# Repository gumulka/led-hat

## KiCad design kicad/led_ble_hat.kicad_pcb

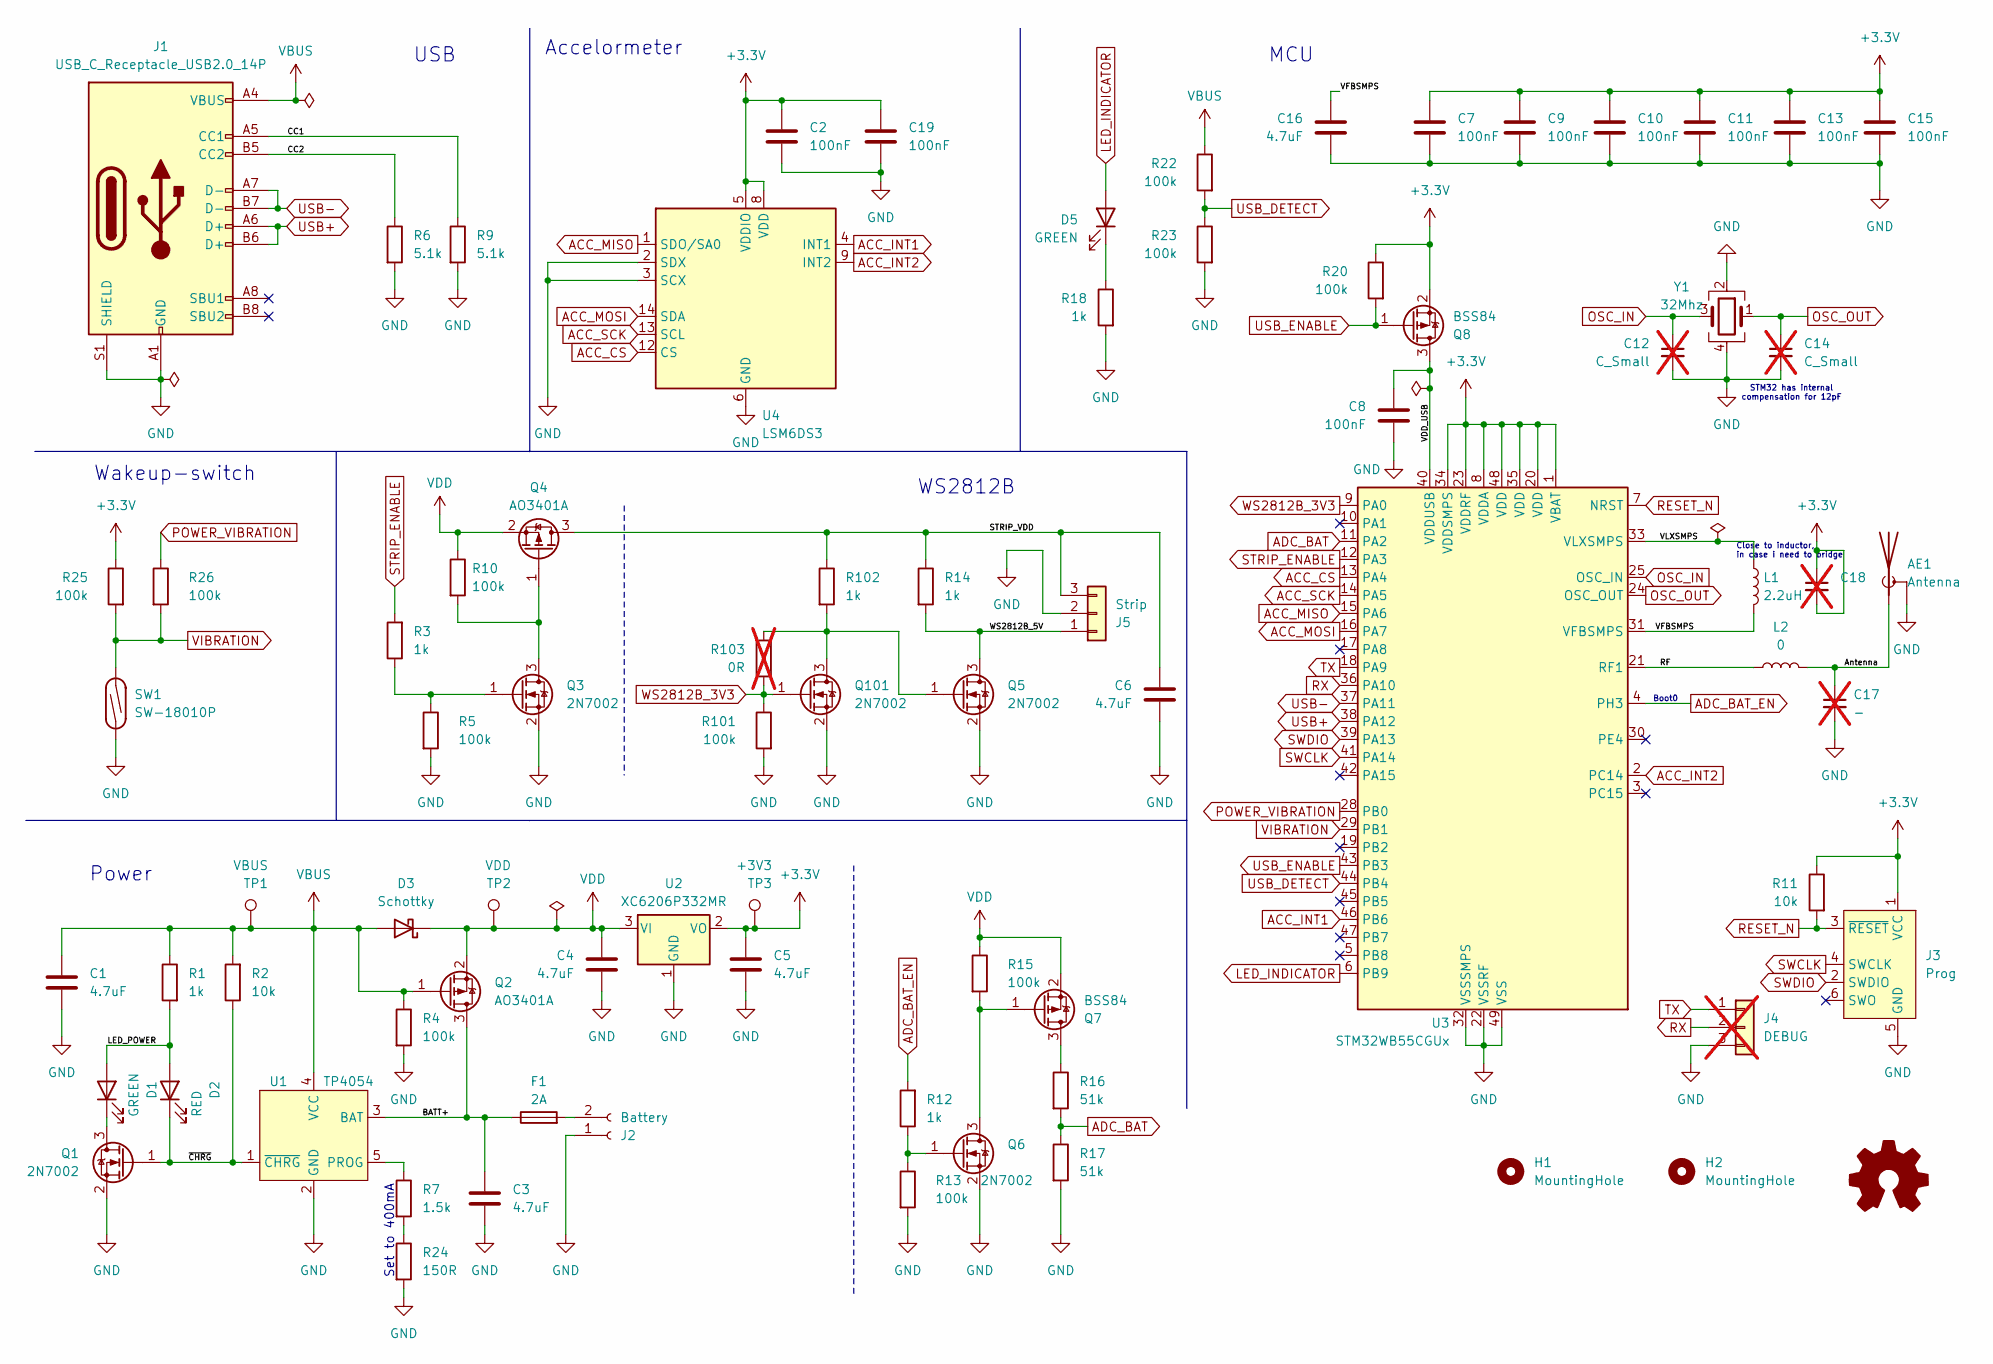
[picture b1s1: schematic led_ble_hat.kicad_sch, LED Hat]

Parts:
AE1: Antenna; Texas_SWRA117D_2.4GHz_Right
C1, C3, C4, C5, C6, C16: 4.7uF; C_0603_1608Metric; LCSC# C19666
C2, C7, C8, C9, C10, C11, C13, C15, C19: 100nF; C_0402_1005Metric; LCSC# C1525
C12, C14: C_Small; C_0402_1005Metric; not fitted
C17: -; C_0402_1005Metric; not fitted
C18: C_0402_1005Metric; not fitted
D1, D5: GREEN; LED_0603_1608Metric; LCSC# C2986059
D2: RED; LED_0603_1608Metric; LCSC# C2286
D3: Schottky; D_SOD-323; LCSC# C191023
F1: 2A; Fuse_0603_1608Metric; LCSC# C187605
H1, H2: MountingHole; MountingHole_2.1mm
J1: USB_C_Receptacle_USB2.0_14P; GSB1C211110DS1HR
J2: Battery; JST_PH_B2B-PH-K_1x02_P2.00mm_Vertical
J3: Prog; Tag-Connect_TC2030-IDC-NL_2x03_P1.27mm_Vertical
J4: DEBUG; PinHeader_1x03_P2.54mm_Vertical_SMD_Pin1Left; not fitted
J5: Strip; JST_PH_B3B-PH-K_1x03_P2.00mm_Vertical
L1: 2.2uH; L_0805_2012Metric; LCSC# C1043
L2: 0; L_0402_1005Metric; LCSC# C17168
Q1, Q3, Q5, Q6, Q101: 2N7002; SOT-23; LCSC# C7420321
Q2, Q4: AO3401A; SOT-23; LCSC# C15127
Q7, Q8: BSS84; SOT-23; LCSC# C7420340
R1, R3, R12, R18: 1k; R_0402_1005Metric; LCSC# C11702
R2, R11: 10k; R_0402_1005Metric; LCSC# C25744
R4, R5, R10, R13, R15, R20, R22, R23, R25, R26, R101: 100k; R_0402_1005Metric; LCSC# C25741
R6, R9: 5.1k; R_0402_1005Metric; LCSC# C25905
R7: 1.5k; R_0402_1005Metric; LCSC# C25867
R14, R102: 1k; R_0603_1608Metric; LCSC# C25803
R16, R17: 51k; R_0402_1005Metric; LCSC# C25794
R24: 150R; R_0402_1005Metric; LCSC# C25082
R103: 0R; R_0402_1005Metric; not fitted
SW1: SW-18010P; SW-18010P_Vertical
TP1: VBUS; TestPoint_Pad_D1.0mm
TP2: VDD; TestPoint_Pad_D1.0mm
TP3: +3V3; TestPoint_Pad_D1.0mm
U1: TP4054; SOT-23-5; LCSC# C32574
U2: XC6206P332MR; SOT-23-3; LCSC# C5446
U3: STM32WB55CGUx; QFN-48-1EP_7x7mm_P0.5mm_EP5.6x5.6mm; LCSC# C404023
U4: LSM6DS3; LGA-14_3x2.5mm_P0.5mm_LayoutBorder3x4y; LCSC# C967633
Y1: 32Mhz; Crystal_SMD_3225-4Pin_3.2x2.5mm; LCSC# C9009

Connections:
+3.3V: C2.2, C5.1, C7.1, C9.1, C10.1, C11.1, C13.1, C15.1, C18.1, C18.2, C19.2, J3.1 (VCC), Q8.2 (S), R11.1, R20.1, R25.1, TP3.1, U2.2 (VO), U3.1 (VBAT), U3.8 (VDDA), U3.20 (VDD), U3.23 (VDDRF), U3.34 (VDDSMPS), U3.35 (VDD), U3.48 (VDD), U4.5 (VDDIO), U4.8 (VDD)
/Antenna: AE1.1 (A), C17.1, L2.2
/BATT+: C3.1, F1.1, Q2.3 (D), U1.3 (BAT)
/CC1: J1.A5 (CC1), R9.1
/CC2: J1.B5 (CC2), R6.1
/LED_POWER: D1.2 (A), D2.2 (A), R1.2
/RF: L2.1, U3.21 (RF1)
/STRIP_VDD: C6.1, J5.3, Q4.3 (D), R14.1, R102.1
/VDD_USB: C8.1, Q8.3 (D), U3.40 (VDDUSB)
/VFBSMPS: C16.1, L1.2, U3.31 (VFBSMPS)
/VLXSMPS: L1.1, U3.33 (VLXSMPS)
/WS2812B_5V: J5.1, Q5.3 (D), R14.2
/~CHRG: D2.1 (K), Q1.1 (G), R2.1, U1.1 (~CHRG)
ACC_CS: U3.13 (PA4), U4.12 (CS)
ACC_INT1: U3.46 (PB6), U4.4 (INT1)
ACC_INT2: U3.2 (PC14), U4.9 (INT2)
ACC_MISO: U3.15 (PA6), U4.1 (SDO/SA0)
ACC_MOSI: U3.16 (PA7), U4.14 (SDA)
ACC_SCK: U3.14 (PA5), U4.13 (SCL)
ADC_BAT: R16.2, R17.1, U3.11 (PA2)
ADC_BAT_EN: R12.2, U3.4 (PH3)
GND: AE1.2 (Shield), C1.2, C2.1, C3.2, C4.2, C5.2, C6.2, C7.2, C8.2, C9.2, C10.2, C11.2, C12.2, C13.2, C14.2, C15.2, C16.2, C17.2, C19.1, J1.A1 (GND), J1.A12 (GND), J1.B1 (GND), J1.B12 (GND), J1.S1 (SHIELD), J2.1, J3.5 (GND), J4.3, J5.2, Q1.2 (S), Q3.2 (S), Q5.2 (S), Q6.2 (S), Q101.2 (S), R4.2, R5.2, R6.2, R9.2, R13.2, R17.2, R18.2, R23.2, R24.2, R101.2, SW1.1, U1.2 (GND), U2.1 (GND), U3.22 (VSSRF), U3.32 (VSSSMPS), U3.49 (VSS), U4.2 (SDX), U4.3 (SCX), U4.6 (GND), U4.7 (GND), Y1.2, Y1.4
LED_INDICATOR: D5.2 (A), U3.6 (PB9)
unnamed: D1.1 (K), Q1.3 (D)
unnamed: D5.1 (K), R18.1
unnamed: F1.2, J2.2
unnamed: Q3.3 (D), Q4.1 (G), R10.2
unnamed: Q3.1 (G), R3.1, R5.1
unnamed: Q6.3 (D), Q7.1 (G), R15.2
unnamed: Q6.1 (G), R12.1, R13.1
unnamed: Q7.3 (D), R16.1
unnamed: Q5.1 (G), Q101.3 (D), R102.2, R103.2
unnamed: R7.2, R24.1
unnamed: R7.1, U1.5 (PROG)
OSC_IN: C12.1, U3.25 (OSC_IN), Y1.3
OSC_OUT: C14.1, U3.24 (OSC_OUT), Y1.1
POWER_VIBRATION: R26.1, U3.28 (PB0)
RESET_N: J3.3 (~RESET), R11.2, U3.7 (NRST)
RX: J4.2, U3.36 (PA10)
STRIP_ENABLE: R3.2, U3.12 (PA3)
SWCLK: J3.4 (SWCLK), U3.41 (PA14)
SWDIO: J3.2 (SWDIO), U3.39 (PA13)
TX: J4.1, U3.18 (PA9)
USB+: J1.A6 (D+), J1.B6 (D+), U3.38 (PA12)
USB-: J1.A7 (D-), J1.B7 (D-), U3.37 (PA11)
USB_DETECT: R22.2, R23.1, U3.44 (PB4)
USB_ENABLE: Q8.1 (G), R20.2, U3.43 (PB3)
VBUS: C1.1, D3.2 (A), J1.A4 (VBUS), J1.A9 (VBUS), J1.B4 (VBUS), J1.B9 (VBUS), Q2.1 (G), R1.1, R2.2, R4.1, R22.1, TP1.1, U1.4 (VCC)
VDD: C4.1, D3.1 (K), Q2.2 (S), Q4.2 (S), Q7.2 (S), R10.1, R15.1, TP2.1, U2.3 (VI)
VIBRATION: R25.2, R26.2, SW1.2, U3.29 (PB1)
WS2812B_3V3: Q101.1 (G), R101.1, R103.1, U3.9 (PA0)

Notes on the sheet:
Set to 400mA
Boot0
STM32 has internal compensation for 12pF
USB
Power
Wakeup-switch
WS2812B
Close to inductor, in case i need to bridge
Accelormeter
MCU

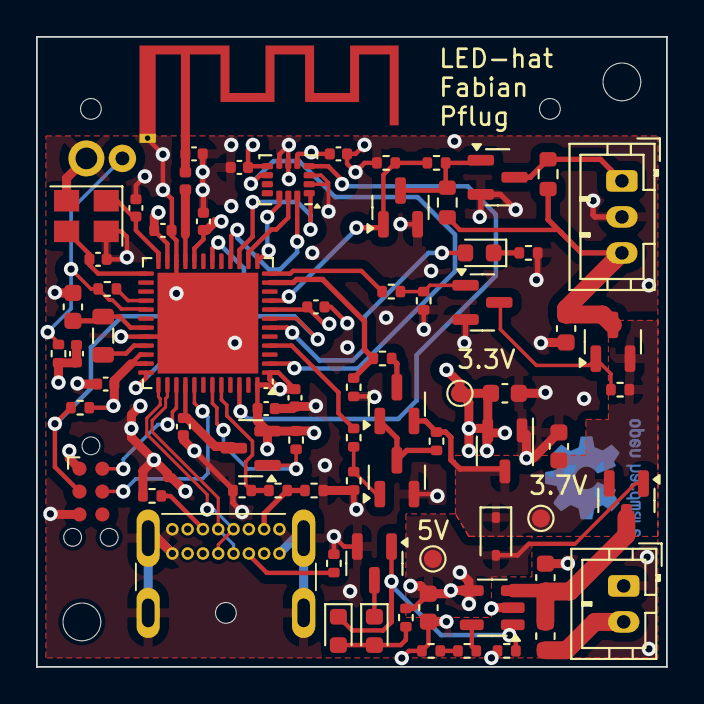
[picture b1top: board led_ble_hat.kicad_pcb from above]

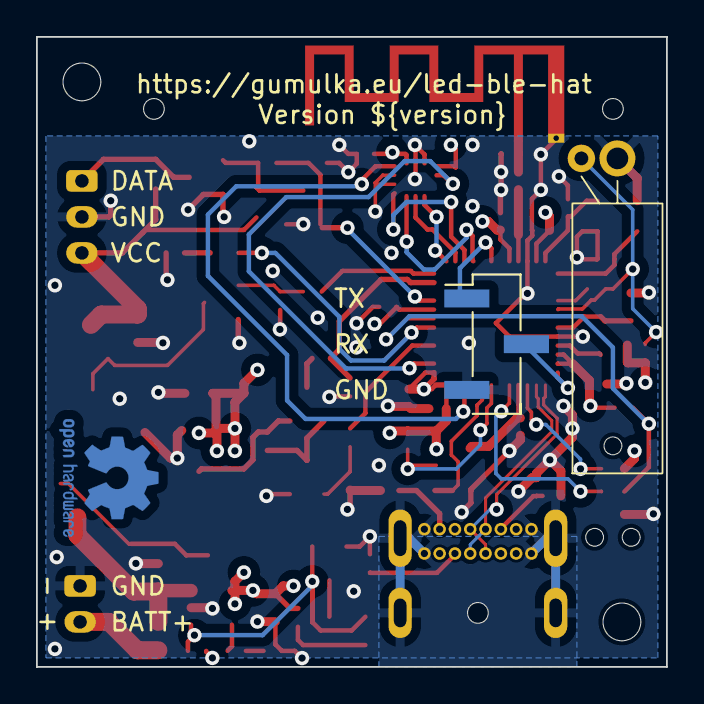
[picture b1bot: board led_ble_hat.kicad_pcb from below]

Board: 4 copper layers, 35.0 x 35.0 mm, 78 parts (2 on the bottom side), 51 nets.

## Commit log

2024-03-03 Move to basic sample of an led-strip
2024-03-03 Add more basic animations
    Animations have a brightness parameter that is currently static, but
    will later be used to adjust the brightness of all the leds.
    Functions return the number of ms to wait between invocations.
2024-03-04 Display random animation on boot
    Display one of the animations at random after reset.
    Add empty animation to display nothing
2024-03-04 Add basic bluetooth device information service
    First service to display something via bluetooth. More to come
2024-03-04 Expose important parameter via bluetooth
    Generate 3 bluetooth characteristics to expose my 3 parameters
    * Speed
    * Brightness
    * Animation
    Parameters can be written and read, as well as subscribed to, to change
    the real time behaviour of the led-strip
2024-03-06 Add more animations
2024-03-07 Add support for STM32WB55 devboard
2024-03-13 Add first draft of schematic for led-hat
    Not quite ready yet, but a good start to work on it later on.
    There is battery management build into, to run on 3.7 V from LiPo or
    use USB as power source.
2024-03-13 Replace battery charging ic, rough pcb placement
    Replaced the battery charging ic with something much simpler.
    Did a rough placement of the component onto a pcb for fit
2024-03-13 Improved routing for PCB
    Also added a vibration sensor on the backside of the PCB
2024-03-14 Add shake detector and final touches
    PCB should be ready to order now.
2024-03-18 Add descriptions for connectors
2024-03-20 Update to Kicad 8
2024-03-20 Move libraries to a submodule
    I want to have a kind of global library with all of my footprints
    and symbols. So submodule for all projects to share footprints
2024-03-20 Add double inverter for ws2812b output
2024-03-22 Add accelerometer
    Add an accellerometer and gyroscope to maybe add animations and energy
    savings based on its output.
2024-03-23 Some final touches
